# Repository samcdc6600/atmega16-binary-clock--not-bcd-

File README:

Note that the file "m16Adef.inc" is not of my own creation and the licensing of
this project does not apply to it. I am not aware of what it's license is.

We assemble simply by issuing the following command (where x.asm is the name of
our assembly file):
    avra x.asm
    
We flash our micro with the following command (this is assumming our flasher's
device file is ugen0.2 and hello.hex is the output of avra that we are
interested in):
   doas avrdude -p m16 -c usbasp -P/dev/ugen0.2 -U flash:w:hello.hex

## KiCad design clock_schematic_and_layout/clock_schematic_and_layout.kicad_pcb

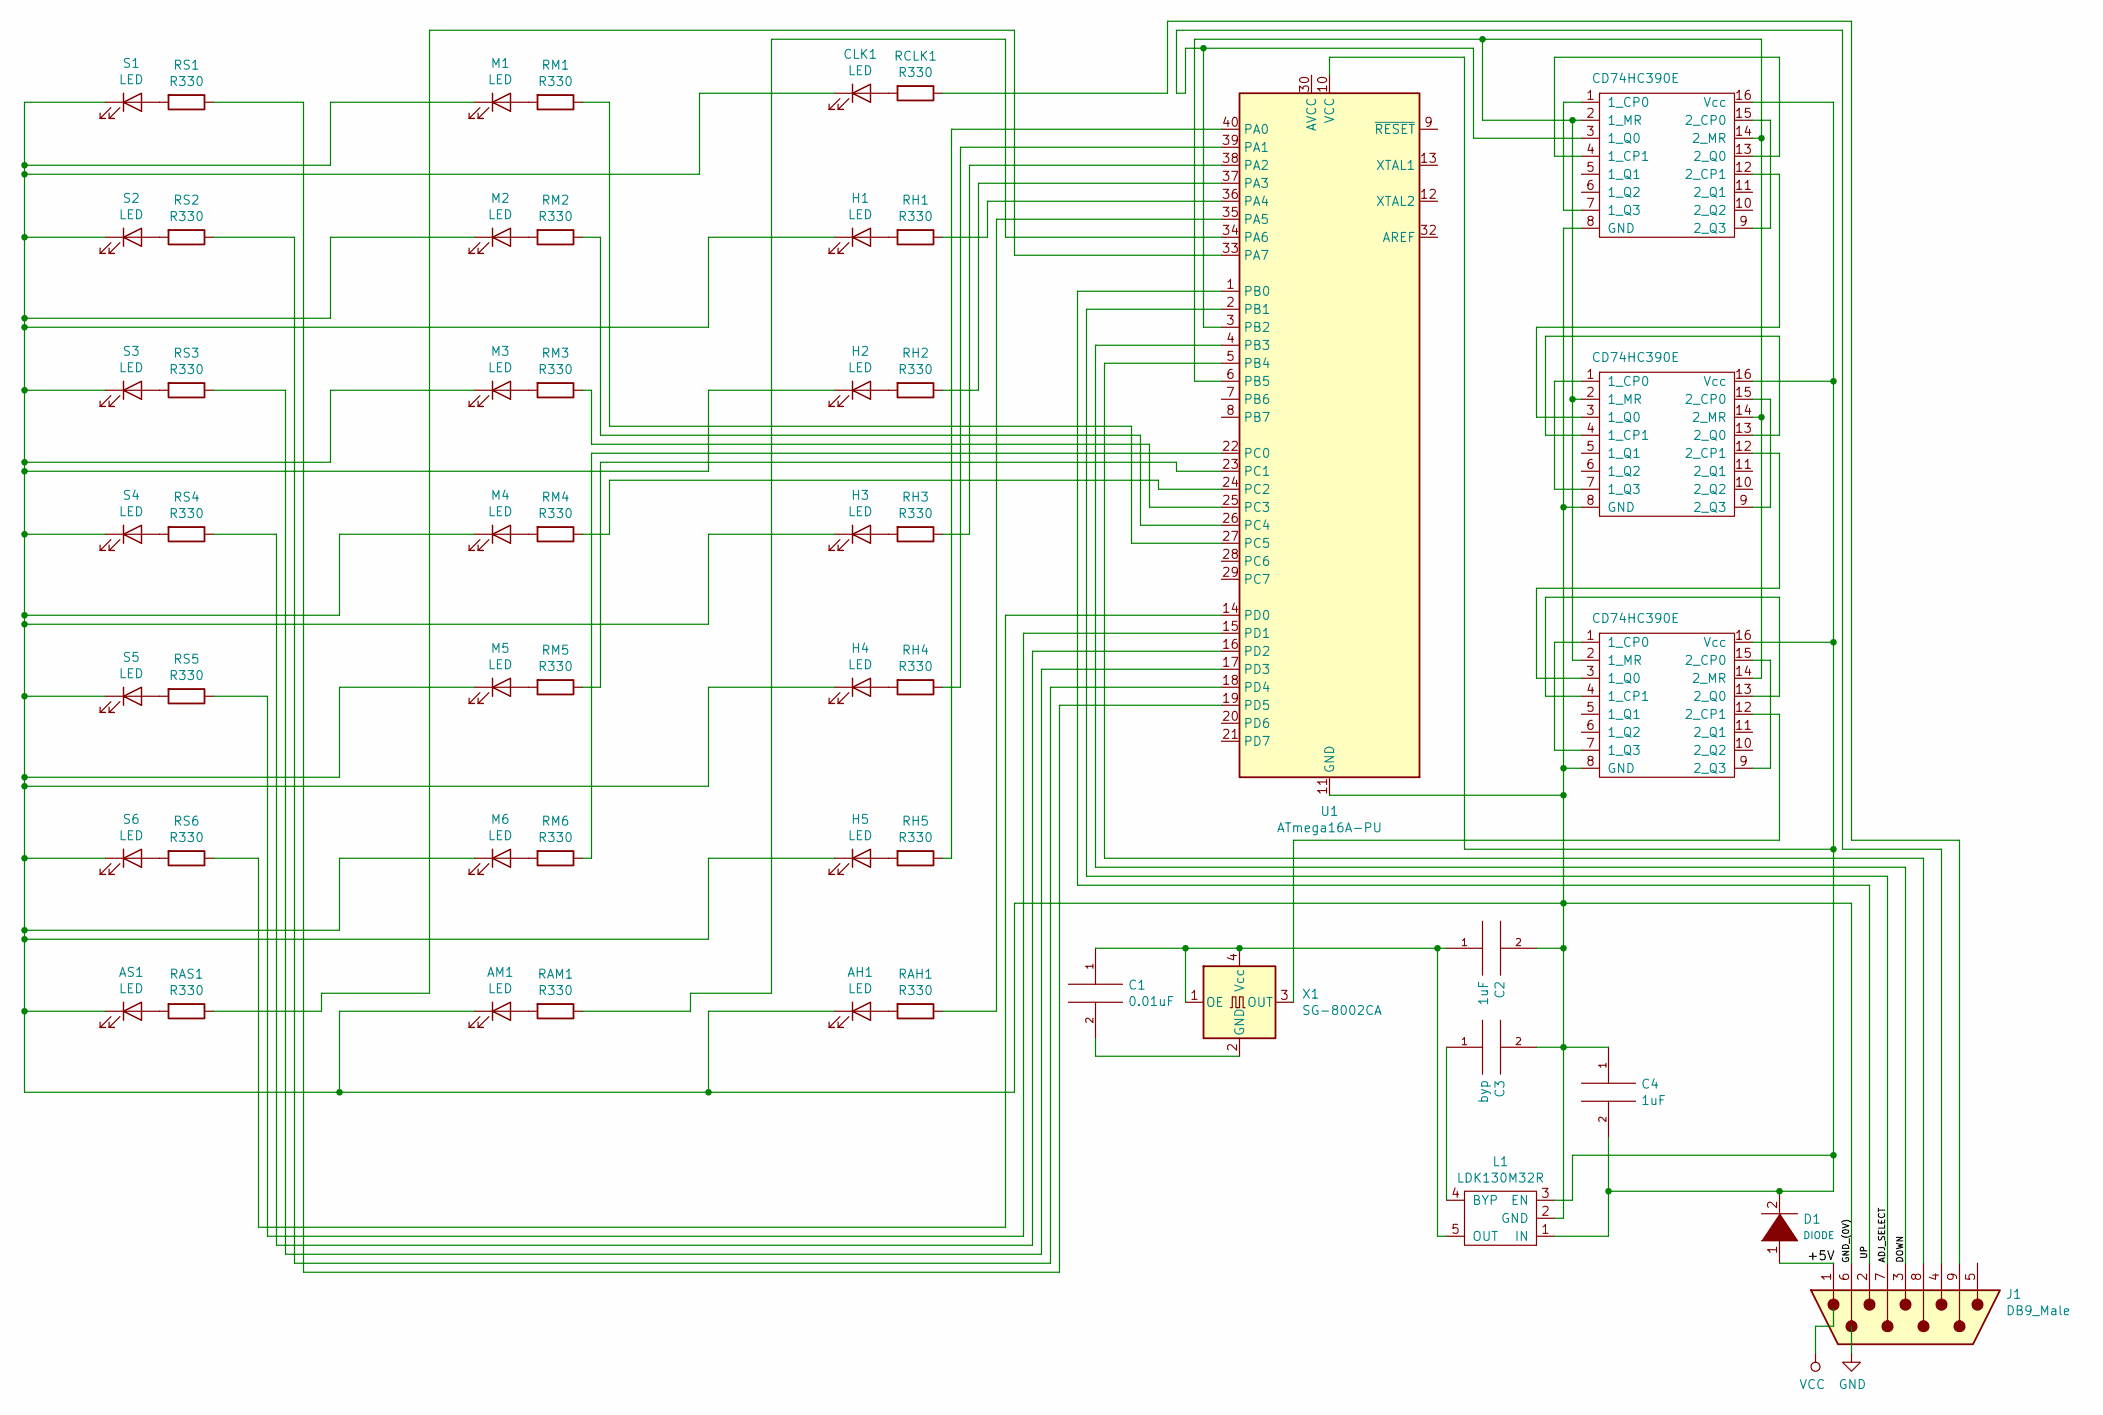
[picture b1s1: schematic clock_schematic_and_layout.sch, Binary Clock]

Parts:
AH1: LED; LED_D3.0mm_Horizontal_O1.27mm_Z2.0mm_Clear
AM1: LED; LED_D3.0mm_Horizontal_O1.27mm_Z2.0mm_Clear
AS1: LED; LED_D3.0mm_Horizontal_O1.27mm_Z2.0mm_Clear
C1: 0.01uF; Crystal_SMD_TXC_9HT11-2Pin_2.0x1.2mm_HandSoldering
C2, C4: 1uF; CP_Radial_D4.0mm_P2.00mm
C3: byp; CP_Radial_D4.0mm_P2.00mm
CD74HC390E1, CD74HC390E2, CD74HC390E3: CD74HC390E; DIP-16_W7.62mm_LongPads
CLK1: LED; LED_D3.0mm_Horizontal_O1.27mm_Z2.0mm_Clear
D1: DIODE; D_MELF-RM10_Universal_Handsoldering
H1, H2, H3, H4, H5: LED; LED_D3.0mm_Horizontal_O1.27mm_Z2.0mm_Clear
J1: DB9_Male; DSUB-9_Female_Horizontal_P2.77x2.84mm_EdgePinOffset7.70mm_H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
L1: LDK130M32R; TSOT-23-5_HandSoldering
M1, M2, M3, M4, M5, M6: LED; LED_D3.0mm_Horizontal_O1.27mm_Z2.0mm_Clear
RAH1: R330; R_Axial_DIN0207_L6.3mm_D2.5mm_P7.62mm_Horizontal
RAM1: R330; R_Axial_DIN0207_L6.3mm_D2.5mm_P7.62mm_Horizontal
RAS1: R330; R_Axial_DIN0207_L6.3mm_D2.5mm_P7.62mm_Horizontal
RCLK1: R330; R_Axial_DIN0207_L6.3mm_D2.5mm_P7.62mm_Horizontal
RH1, RH2, RH3, RH4, RH5: R330; R_Axial_DIN0207_L6.3mm_D2.5mm_P7.62mm_Horizontal
RM1, RM2, RM3, RM4, RM5, RM6: R330; R_Axial_DIN0207_L6.3mm_D2.5mm_P7.62mm_Horizontal
RS1, RS2, RS3, RS4, RS5, RS6: R330; R_Axial_DIN0207_L6.3mm_D2.5mm_P7.62mm_Horizontal
S1, S2, S3, S4, S5, S6: LED; LED_D3.0mm_Horizontal_O1.27mm_Z2.0mm_Clear
U1: ATmega16A-PU; DIP-40_W15.24mm
X1: SG-8002CA; Oscillator_SMD_SeikoEpson_SG8002CA-4Pin_7.0x5.0mm_HandSolde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

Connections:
/+5V: D1.1 (K), J1.1
/ADJ_SELECT: J1.7, U1.2 (PB1)
/DOWN: J1.3, U1.4 (PB3)
/GND_(0V): AH1.1 (K), AM1.1 (K), AS1.1 (K), C2.2, C3.2, C4.1, CD74HC390E1.8 (GND), CD74HC390E2.8 (GND), CD74HC390E3.8 (GND), CLK1.1 (K), H1.1 (K), H2.1 (K), H3.1 (K), H4.1 (K), H5.1 (K), J1.6, L1.2 (GND), M1.1 (K), M2.1 (K), M3.1 (K), M4.1 (K), M5.1 (K), M6.1 (K), S1.1 (K), S2.1 (K), S3.1 (K), S4.1 (K), S5.1 (K), S6.1 (K), U1.11 (GND), U1.31 (GND)
/UP: J1.2, U1.1 (PB0)
unnamed: AH1.2 (A), RAH1.2
unnamed: AM1.2 (A), RAM1.2
unnamed: AS1.2 (A), RAS1.2
unnamed: C1.1, C2.1, L1.5 (OUT), X1.1 (OE), X1.4 (Vcc)
unnamed: C1.2, X1.2 (GND)
unnamed: C3.1, L1.4 (BYP)
unnamed: C4.2, CD74HC390E1.16 (Vcc), CD74HC390E2.16 (Vcc), CD74HC390E3.16 (Vcc), D1.2 (A), L1.1 (IN), L1.3 (EN), U1.10 (VCC)
unnamed: CD74HC390E1.1 (1_CP0), CD74HC390E1.7 (1_Q3)
unnamed: CD74HC390E1.3 (1_Q0), J1.4, U1.3 (PB2)
unnamed: CD74HC390E1.12 (2_CP1), CD74HC390E2.3 (1_Q0)
unnamed: CD74HC390E1.4 (1_CP1), CD74HC390E1.13 (2_Q0)
unnamed: CD74HC390E1.2 (1_MR), CD74HC390E1.14 (2_MR), CD74HC390E2.2 (1_MR), CD74HC390E2.14 (2_MR), CD74HC390E3.2 (1_MR), CD74HC390E3.14 (2_MR), U1.6 (PB5)
unnamed: CD74HC390E1.9 (2_Q3), CD74HC390E1.15 (2_CP0)
unnamed: CD74HC390E2.1 (1_CP0), CD74HC390E2.7 (1_Q3)
unnamed: CD74HC390E2.12 (2_CP1), CD74HC390E3.3 (1_Q0)
unnamed: CD74HC390E2.4 (1_CP1), CD74HC390E2.13 (2_Q0)
unnamed: CD74HC390E2.9 (2_Q3), CD74HC390E2.15 (2_CP0)
unnamed: CD74HC390E3.1 (1_CP0), CD74HC390E3.7 (1_Q3)
unnamed: CD74HC390E3.12 (2_CP1), X1.3 (OUT)
unnamed: CD74HC390E3.4 (1_CP1), CD74HC390E3.13 (2_Q0)
unnamed: CD74HC390E3.9 (2_Q3), CD74HC390E3.15 (2_CP0)
unnamed: CLK1.2 (A), RCLK1.2
unnamed: H1.2 (A), RH1.2
unnamed: H2.2 (A), RH2.2
unnamed: H3.2 (A), RH3.2
unnamed: H4.2 (A), RH4.2
unnamed: H5.2 (A), RH5.2
unnamed: J1.8, U1.5 (PB4)
unnamed: J1.9, RCLK1.1
unnamed: M1.2 (A), RM1.2
unnamed: M2.2 (A), RM2.2
unnamed: M3.2 (A), RM3.2
unnamed: M4.2 (A), RM4.2
unnamed: M5.2 (A), RM5.2
unnamed: M6.2 (A), RM6.2
unnamed: RAH1.1, U1.35 (PA5)
unnamed: RAM1.1, U1.34 (PA6)
unnamed: RAS1.1, U1.33 (PA7)
unnamed: RH1.1, U1.36 (PA4)
unnamed: RH2.1, U1.37 (PA3)
unnamed: RH3.1, U1.38 (PA2)
unnamed: RH4.1, U1.39 (PA1)
unnamed: RH5.1, U1.40 (PA0)
unnamed: RM1.1, U1.27 (PC5)
unnamed: RM2.1, U1.26 (PC4)
unnamed: RM3.1, U1.25 (PC3)
unnamed: RM4.1, U1.24 (PC2)
unnamed: RM5.1, U1.23 (PC1)
unnamed: RM6.1, U1.22 (PC0)
unnamed: RS1.1, U1.19 (PD5)
unnamed: RS1.2, S1.2 (A)
unnamed: RS2.1, U1.18 (PD4)
unnamed: RS2.2, S2.2 (A)
unnamed: RS3.1, U1.17 (PD3)
unnamed: RS3.2, S3.2 (A)
unnamed: RS4.1, U1.16 (PD2)
unnamed: RS4.2, S4.2 (A)
unnamed: RS5.1, U1.15 (PD1)
unnamed: RS5.2, S5.2 (A)
unnamed: RS6.1, U1.14 (PD0)
unnamed: RS6.2, S6.2 (A)

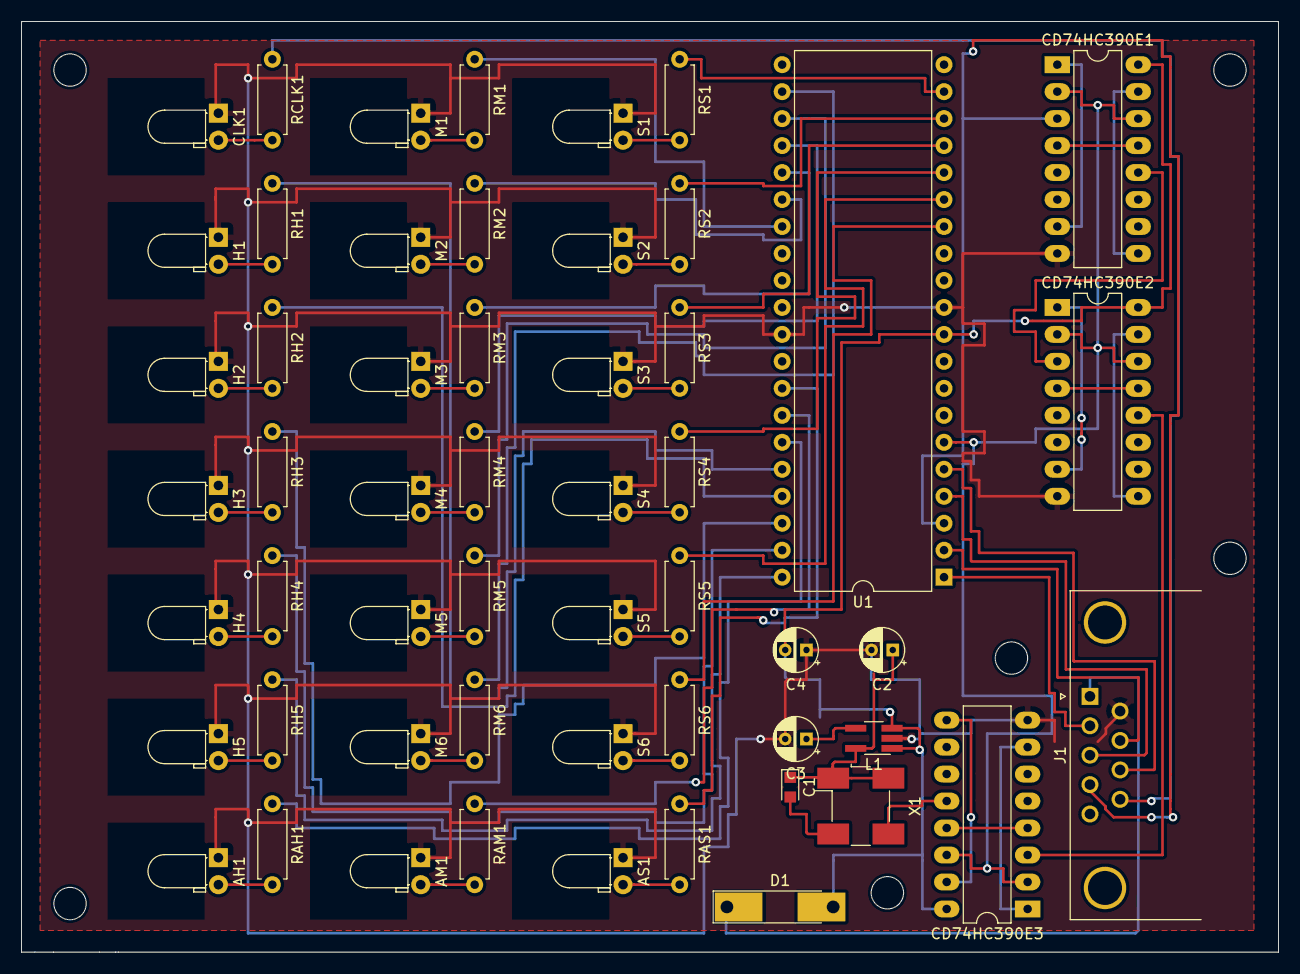
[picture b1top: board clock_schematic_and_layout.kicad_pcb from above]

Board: 2 copper layers, 118.4 x 87.6 mm, 54 parts (0 on the bottom side), 66 nets.

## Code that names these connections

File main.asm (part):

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	;; We set all pins for ports PA, PC and PD to outputs so we dont have to
	;; worry about pull ups to save power on the pins we are not actually
	;; using, that is assuming it works like that :)
	.equ	ddrSecondPins = 0b11111111	; Pins PD0 - PD7 (PD0 - PD5 used)
	.equ	ddrMinutePins = 0b11111111 ; Pins PC7 - PC0 (PC5 - PC0 used)
	;; Pins PA0 - PA7 (PA0 - PA4 used for hours and PA5 - PA7 used for
	;; adjust LED Indicator Pins)
	.equ	ddrHourAndAdjustLEDIndicatorPins = 0b11111111
	;; For changing the time. Pins PB0 - PB7 (PB0, PB1, PB3 and PB4 used as
	.equ	ddrAdjustPins = 0b00100000 ; input and PB5 used as output
	;; Enable the pullups for PB (except for PB2 (as it is active high) and
	;; PB5 (we set this low as it is used to toggle master reset 1 (1mr) on
	;; the decade counter the ocsilator is connected to (it is active high))
	.equ	adjustPinsPullups = 0b11011011 ; ocsilator)
	.equ	adjustPinsPullupsMR1High = 0b11111011
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	.equ	adjustHoursLEDIndicatorPin = 0b00100000
	;; To dissable (mask out) adjust LEDS
	.equ	noAdjustLEDs = 0b00011111
	;; To mask out PB2 (INT2) and PA5 (1mr)
	.equ	noInt2Or1Mr = 0b11011011
	;; To enable int 2 (pin PB2)
	.equ	int2En = 0b00100000
	;; Adjust input masks
	.equ	adjustUpPin = 0b11011010
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	ldi	r16, low(ddrAdjustPins)
	;; Set the Data Direction Register for Port B (time adjustment controls
	;; and time signal)
	out	DDRB, r16	; Also note that PB2 is used for our time signal
	ldi	r16, low(adjustPinsPullups)
	; Set pull up's high (except for PB2 (time signal) which is active high)
	out	PortB, r16
	
	ldi	r16, low(int2En)
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	ret


	;; DISABLE_JTAG dissables the JTAG interface (PC7 - PC2) in software.
	;; This allows the use of the PC7 - PC2 pins as general IO while still
	;; allowing the chip to be programmed as we have not set any fuses.
	;; The manual says to set the JTD bit (bit 7 according to the manual (pg
	;; 236) but that does not seem to work.) Post #3 on this site:
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ADJUSTING_DELAY:		;===============================================
 	cli			; Dissable interrupts
	;; We do this here and not after "brne	WAIT_FOR_USER_INPUT" because
	;; interrups seem to be re-enabled (when PB0 is low) randomly after
	;; the PB0 pin is held low or strobed enough when adjusting minutes,
	;; causing the seconds count to increment. We cannot figure it out.
	;; We think it may even be an electrical problem although we hope not.
	;; It seems to take different times for different chips :/
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
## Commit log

2020-01-03 No working code yet. Just an initial commit to save what we have and so that we actually have somehting.
2020-01-07 We have implemented the basic clock functionality. Now we need to implement the time adjustment functionality.
2020-01-09 We have implemented the time chaning functionality to some extent. It is not fully functional yet however. The code from this commit should not be used as it.
2020-01-09 Fixed a couple of bugs. There are still a couple (that I know of) that need fixing however.
2020-01-11 We have fixed a couple of bugs but have also introduced a regression regarding the automated updating of time. We will be using the stack from now on to provide more isolation for our sub rutines. We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
2020-01-13 Fixed bug with hourCount being corrupted with currentlyAdjusting value.
2020-01-13 removed some stuff to ensure merging is easier
2020-01-13 "There is a bit of oddness when exiting the adjusting mode in terms of the seconds LEDs changing faster then they should. However we thing that the overall timming is correct. There is a very strange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
2020-01-13 We have added a workaround for the terrible functionality breaking bug described in the last commit. Although we wish we could figour out the root cause :'(. Our fix involves enabling 1MR on our coun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
2020-01-14 Fixed error in commente and added partialy finished schematic
2020-01-14 Made further adjustment to comment.
2020-01-18 Removed erronious jump from ADJUST_TIME_DOWN_PROPER sub routine (also have done more work on schematics)
2020-01-22 We have done some more work on the schematics and stuff
2020-01-26 Finished schematic and PCB layout. Haven't properly double checked the schematic though :'( (can't be bothered haha.)
